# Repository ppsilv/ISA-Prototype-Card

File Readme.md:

## Kicad 7.0 Standard prototype board

To fit into 10cm x 10cm needs adjustments.

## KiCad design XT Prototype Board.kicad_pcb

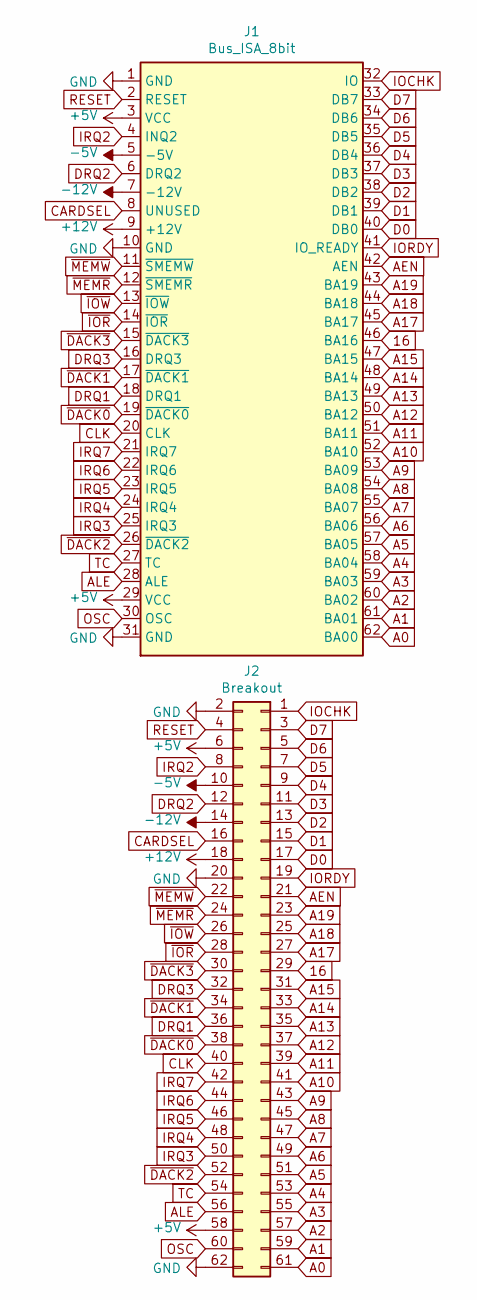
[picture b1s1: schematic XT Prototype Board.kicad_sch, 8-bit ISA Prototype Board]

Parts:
J1: Bus_ISA_8bit; Conn_Edge_PCB_ISA8
J2: Breakout; PinHeader_2x31_P2.54mm_Vertical

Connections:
16: J1.46 (BA16), J2.29
+5V: J1.3 (VCC), J1.29 (VCC), J2.6, J2.58
+12V: J1.9 (+12V), J2.18
-5V: J1.5 (-5V), J2.10
-12V: J1.7 (-12V), J2.14
A0: J1.62 (BA00), J2.61
A1: J1.61 (BA01), J2.59
A2: J1.60 (BA02), J2.57
A3: J1.59 (BA03), J2.55
A4: J1.58 (BA04), J2.53
A5: J1.57 (BA05), J2.51
A6: J1.56 (BA06), J2.49
A7: J1.55 (BA07), J2.47
A8: J1.54 (BA08), J2.45
A9: J1.53 (BA09), J2.43
A10: J1.52 (BA10), J2.41
A11: J1.51 (BA11), J2.39
A12: J1.50 (BA12), J2.37
A13: J1.49 (BA13), J2.35
A14: J1.48 (BA14), J2.33
A15: J1.47 (BA15), J2.31
A17: J1.45 (BA17), J2.27
A18: J1.44 (BA18), J2.25
A19: J1.43 (BA19), J2.23
AEN: J1.42 (AEN), J2.21
ALE: J1.28 (ALE), J2.56
CARDSEL: J1.8 (UNUSED), J2.16
CLK: J1.20 (CLK), J2.40
D0: J1.40 (DB0), J2.17
D1: J1.39 (DB1), J2.15
D2: J1.38 (DB2), J2.13
D3: J1.37 (DB3), J2.11
D4: J1.36 (DB4), J2.9
D5: J1.35 (DB5), J2.7
D6: J1.34 (DB6), J2.5
D7: J1.33 (DB7), J2.3
DRQ1: J1.18 (DRQ1), J2.36
DRQ2: J1.6 (DRQ2), J2.12
DRQ3: J1.16 (DRQ3), J2.32
GND: J1.1 (GND), J1.10 (GND), J1.31 (GND), J2.2, J2.20, J2.62
IOCHK: J1.32 (IO), J2.1
IORDY: J1.41 (IO_READY), J2.19
IRQ2: J1.4 (INQ2), J2.8
IRQ3: J1.25 (IRQ3), J2.50
IRQ4: J1.24 (IRQ4), J2.48
IRQ5: J1.23 (IRQ5), J2.46
IRQ6: J1.22 (IRQ6), J2.44
IRQ7: J1.21 (IRQ7), J2.42
OSC: J1.30 (OSC), J2.60
RESET: J1.2 (RESET), J2.4
TC: J1.27 (TC), J2.54
~DACK0: J1.19 (~DACK0), J2.38
~DACK1: J1.17 (~DACK1), J2.34
~DACK2: J1.26 (~DACK2), J2.52
~DACK3: J1.15 (~DACK3), J2.30
~IOR: J1.14 (~IOR), J2.28
~IOW: J1.13 (~IOW), J2.26
~MEMR: J1.12 (~SMEMR), J2.24
~MEMW: J1.11 (~SMEMW), J2.22

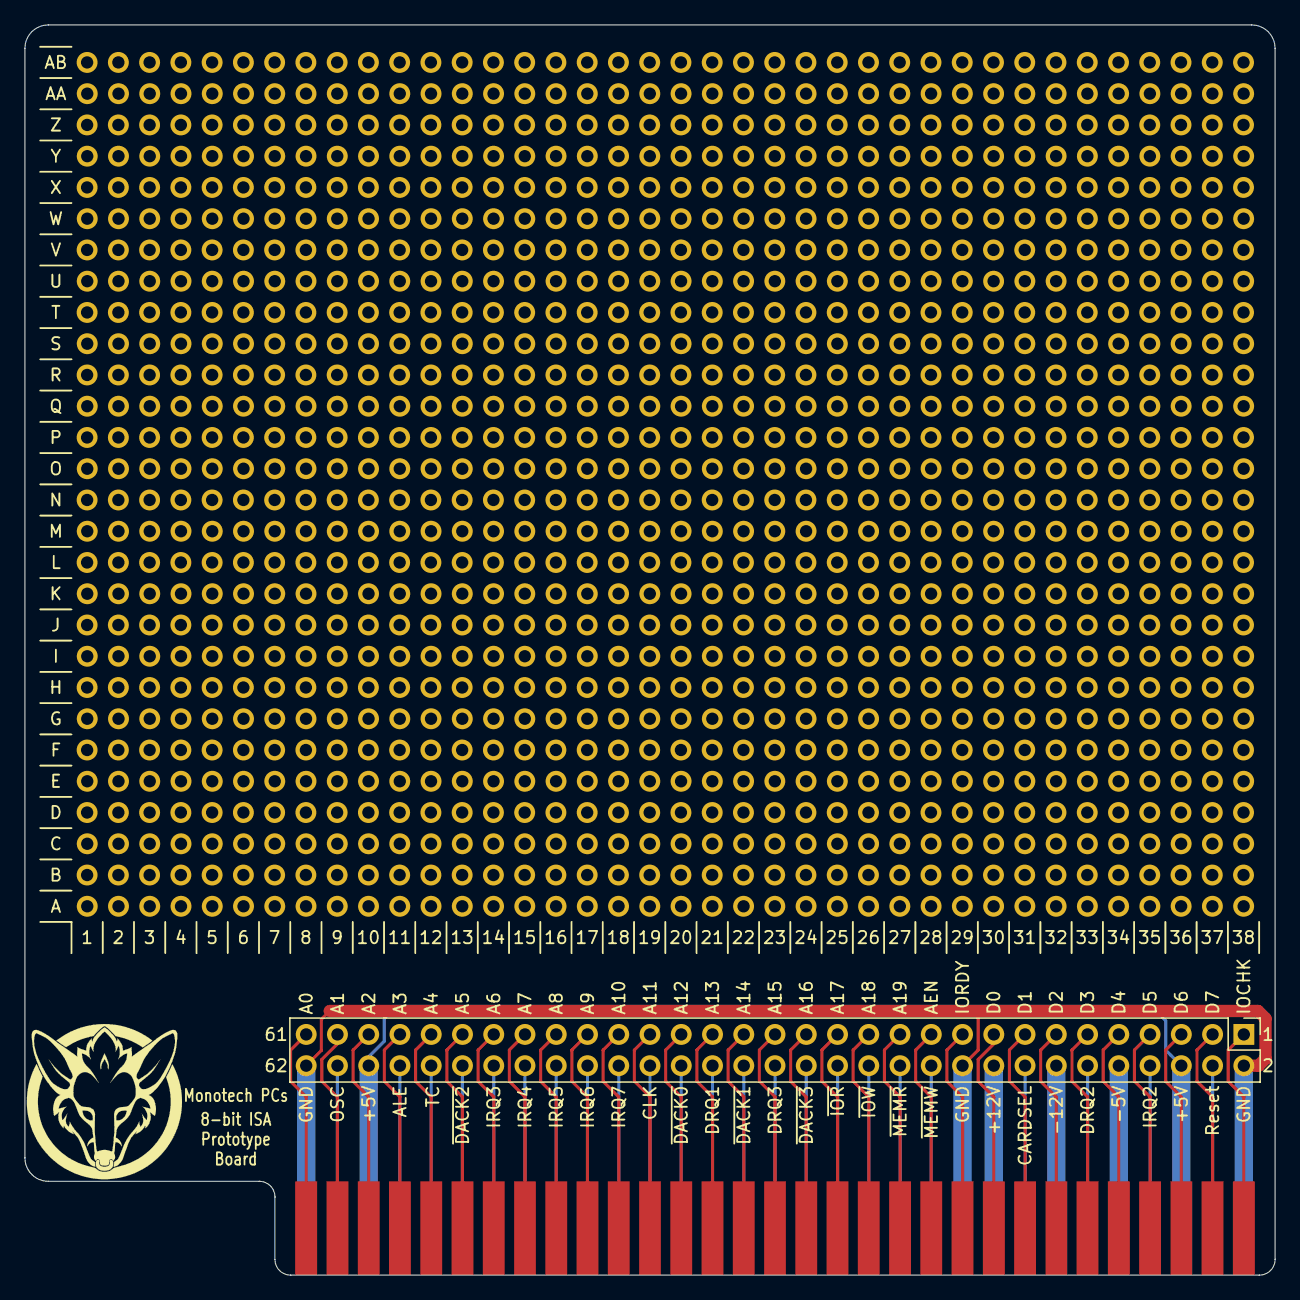
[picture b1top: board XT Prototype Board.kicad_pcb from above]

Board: 2 copper layers, 101.6 x 101.6 mm, 4 parts (1 on the bottom side), 59 nets.

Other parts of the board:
LOGO1, LOGO2: LOGO; Monotech Logo 12.7mm

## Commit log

2025-04-13 updated to kicad 7.0
